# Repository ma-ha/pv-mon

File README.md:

# Monitor Photovoltaic (PV) System with LiFePO4 Batteries

Measure:
1. LiFePo4 cell and block voltage
2. Current and voltage from solar panel strings
3. 230 V output current 
4. 230 V fallback current

Send data via WiFi to local "IoT Server" and make data accessible in InfluxDB.

_STATUS: WIP, partially tested_

LiFePO4 (aka LFP) batteries are known as safe and the voltages may not be dangerous for humans.

**BUT ... WARNING: LFP batteries contain a lot of Energy! Shorts can cause enormous sparks, melt metal and cause fire.**

Check your circuits twice for shorts (soldering problems)! 
Be careful touching the circuit with metal tools (e.g. multimeter tips).
Put the circuit in a safe enclosure!

# Sensor Device

The device measures up to 16 voltages and sends them to the IoT Server. 

Hardware is cheap and simple, based on:
- an ESP8266 "D1 Mini" controller with WIFI
- a CD74HC4067 as 16 channel (or 74HC4051 as 8 channel) multiplexer board
- Pololu D36V6F3 Step-Down Voltage Regulator for 3.3 V supply

The sensor is designed to connect via a "8s JST XH " y-splitter cable between the
battery and the BMS. 
Alternatively connect Pin1 to "minus", Pin2 to the plus of 1st cell, Pin3 to the plus of 2nd cell and so on.

## Sensor Firmware

To upload the [firmware](sensor16ADC/bat-mon-firmware/bat-mon-firmware.ino) 
to the "D1 Mini" via the Arduino IDE, you must 
add `http://arduino.esp8266.com/stable/package_esp8266com_index.json` as 
"Additiona Boards Manager URLs" in the "File" > "Settings" menu. 
Then install the newest version in "Tools" > "Board" > "Board Manager" the "esp8266".
For me the "NodeMCU v0.9" board works fine.

Then just 
- connect the D1 Mini via USB 
- double click the [bat-mon-firmware.ino](sensor16ADC/bat-mon-firmware/bat-mon-firmware.ino) 
  to oben it in the Arduino IDE and 
- click the "Upload" button to compile the code and program the module

The sensor will read out the voltages once per minute and send them to the "IoT API Server".

WARNING: If you use the Arduino IDE for NodeMCU, you will overwrite the LUA SDK. 
If you want back the Lua SDK, use the “flasher” to re-install the firmware. 
You can download the flasher from their Github page https://github.com/nodemcu/nodemcu-flasher.

# Server Set Up

The "server" (a PC is ok) need to run an "[IoT API Server](iot-api-server/app.js)", 
where the sensors post readings data and an InfluxDB to store and analyze the data.

To make things as easy, I recommend to run the server and the DB as Docker containers.

## InfluxDB

The Influx DB stores the sensor data as timelines. 
You can query data and show data as graphs on dashboards using your browser.

Prepare a folders for DB, e.g. 

    mkdir ~/influxdb2
    cd ~/influxdb2
    mkdir db
    mkdir config
    export DB_DIR=$PWD

Start InfluxDB docker server:

    docker run -p 8086:8086 -d --restart=always --name influxdb \
      -v $DB_DIR/db:/var/lib/influxdb2 \
      -v $DB_DIR/config:/etc/influxdb2 \
      -e DOCKER_INFLUXDB_INIT_USERNAME=mysuerpadmin \
      -e DOCKER_INFLUXDB_INIT_PASSWORD=mysuerpadminpassord \
      -e DOCKER_INFLUXDB_INIT_ORG=my-org \
      -e DOCKER_INFLUXDB_INIT_BUCKET=pv \
      influxdb:2.1-alpine

Open http://localhost:8086 in your browser and finalize the set up.

Finally create or copy an API token for the API server, via "Data" manu and "API Tokens" tab.

## IoT API Server 

The "[API Server](iot-api-server/app.js)" is a tiny JS app and listens on 8899.

Devices can post JSON data to the endpoint 
`http:/server-ip:8899/<bucket>/<data-type>?key=<api-key>`

JSON data is e.g.:

    { src: 'Bat1_7', fld: 'U', val: 0.06 }

## Start on Console

Put the InfluxDB API key into the two YAML files in the `iot-api-server/config/` dir.

If you modify the `API_KEY`, don't forget to chage that also in the `bat-mon-firmware.ino`.

To start the server on the console for testing, execute:

    cd iot-api-server
    npm install
    export NODE_ENV=DEV
    node app.js

To send some test data execute: `mocha test/testPostApiSvr.js`

## Run as Docker Server

Build and install the IoT API Server:

    cd iot-api-server
    docker build -t mh/iot-api-server . 
    docker rm iot-api-server
    docker run -d -e NODE_ENV=MAIN --link influxdb:influxdb  -p 8899:8899  --name iot-api-server  mh/iot-api-server

To send some test data execute (require `npm install -g mocha` once): 

    export NODE_ENV=DEV
    mocha test/testPostApiSvr.js

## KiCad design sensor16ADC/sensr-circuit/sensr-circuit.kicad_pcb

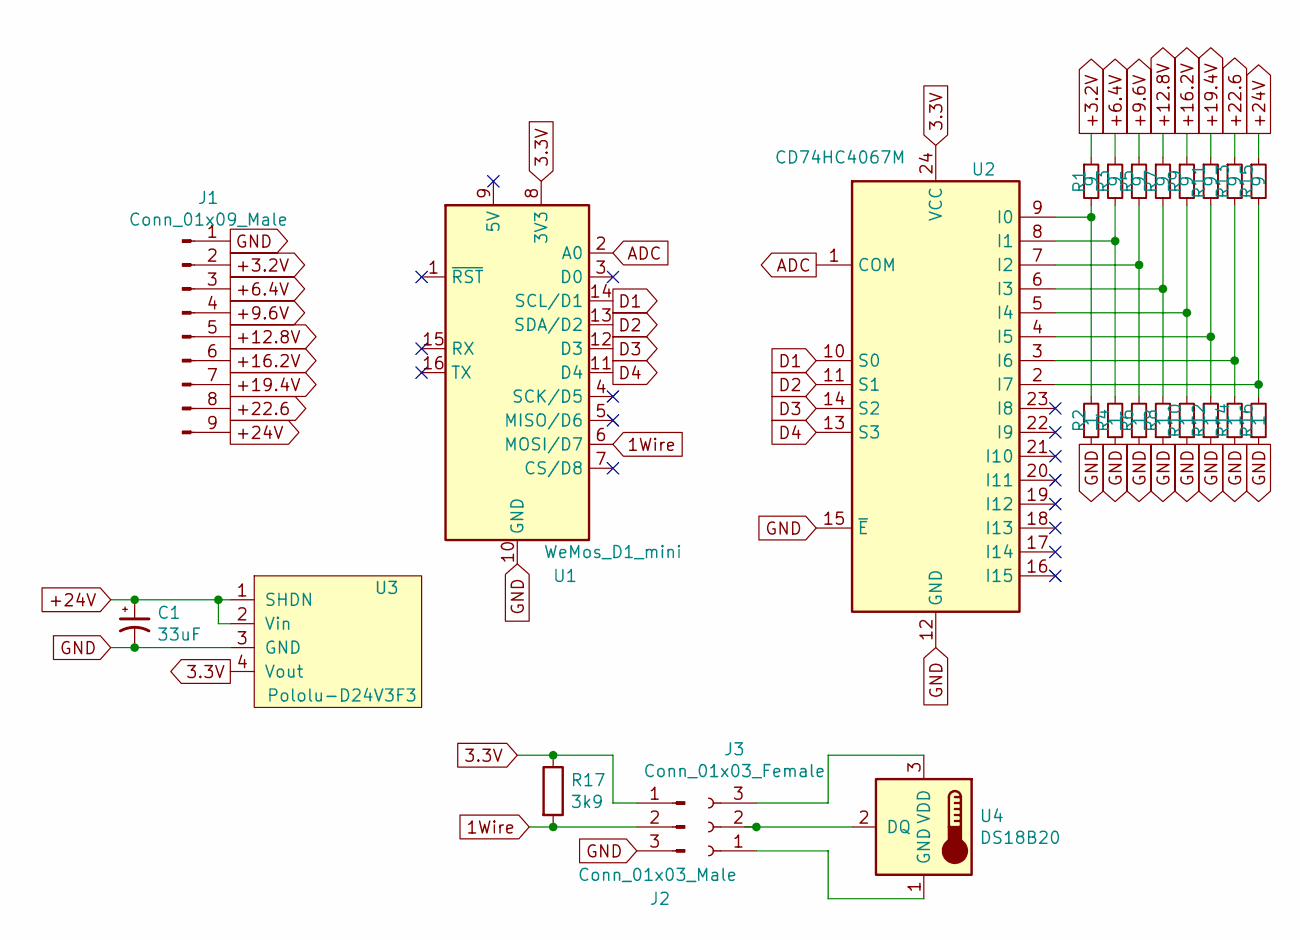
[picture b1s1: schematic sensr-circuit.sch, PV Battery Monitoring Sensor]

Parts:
C1: 33uF; CP_Radial_D5.0mm_P2.50mm
J1: Conn_01x09_Male; PinHeader_1x09_P2.54mm_Vertical
J2: Conn_01x03_Male; JST_EH_B3B-EH-A_1x03_P2.50mm_Vertical
J3: Conn_01x03_Female
R1, R3, R5, R7, R9, R11, R13, R15: 9; R_Axial_DIN0204_L3.6mm_D1.6mm_P7.62mm_Horizontal
R2, R4, R6, R8, R10, R12, R14, R16: 1; R_Axial_DIN0204_L3.6mm_D1.6mm_P7.62mm_Horizontal
R17: 3k9; R_Axial_DIN0309_L9.0mm_D3.2mm_P2.54mm_Vertical
U1: WeMos_D1_mini; WEMOS_D1_mini_light
U2: CD74HC4067M; 74HC4067DB
U3: Pololu-D24V3F3
U4: DS18B20

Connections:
1Wire: J2.2, R17.2, U1.6 (MOSI/D7)
3.3V: J2.1, R17.1, U1.8 (3V3), U2.24 (VCC), U3.4 (Vout)
+3.2V: J1.2, R1.1
+6.4V: J1.3, R3.1
+9.6V: J1.4, R5.1
+12.8V: J1.5, R7.1
+16.2V: J1.6, R9.1
+19.4V: J1.7, R11.1
+22.6: J1.8, R13.1
+24V: C1.1, J1.9, R15.1, U3.1 (SHDN), U3.2 (Vin)
ADC: U1.2 (A0), U2.1 (COM)
D1: U1.14 (SCL/D1), U2.10 (S0)
D2: U1.13 (SDA/D2), U2.11 (S1)
D3: U1.12 (D3), U2.14 (S2)
D4: U1.11 (D4), U2.13 (S3)
GND: C1.2, J1.1, J2.3, R2.1, R4.1, R6.1, R8.1, R10.1, R12.1, R14.1, R16.1, U1.10 (GND), U2.12 (GND), U2.15 (~E), U3.3 (GND)
unnamed: J3.1, U4.1 (GND)
unnamed: J3.2, U4.2 (DQ)
unnamed: J3.3, U4.3 (VDD)
unnamed: R1.2, R2.2, U2.9 (I0)
unnamed: R3.2, R4.2, U2.8 (I1)
unnamed: R5.2, R6.2, U2.7 (I2)
unnamed: R7.2, R8.2, U2.6 (I3)
unnamed: R9.2, R10.2, U2.5 (I4)
unnamed: R11.2, R12.2, U2.4 (I5)
unnamed: R13.2, R14.2, U2.3 (I6)
unnamed: R15.2, R16.2, U2.2 (I7)

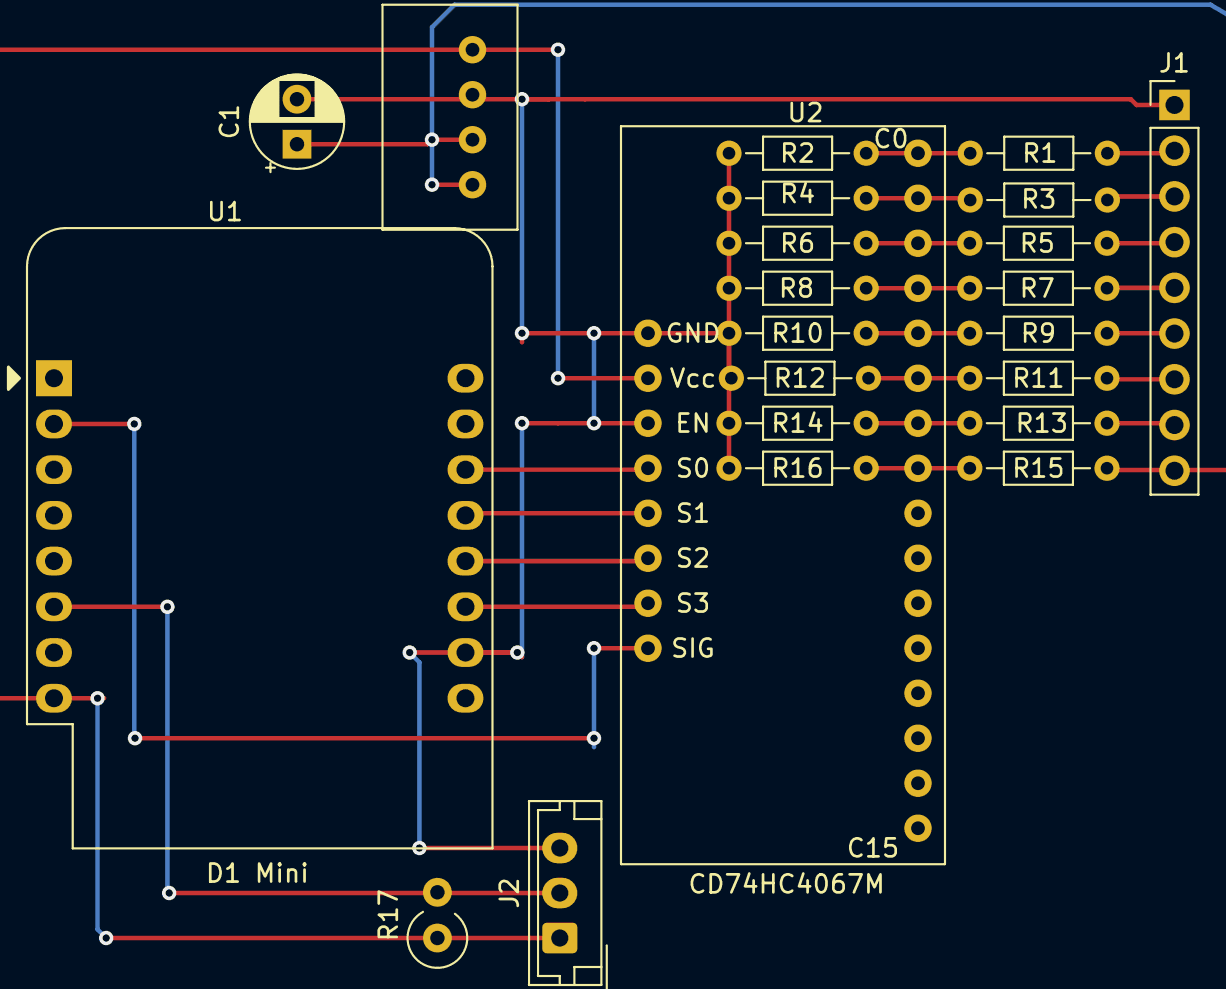
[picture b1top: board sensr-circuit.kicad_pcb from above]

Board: 2 copper layers, 23 parts (0 on the bottom side), 24 nets.

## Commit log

2022-03-20 publish 1st working version
2022-03-20 lazout for prototype board
2022-03-20 improve docu
2022-03-20 improved docu
2022-03-20 bat-mon-firmware:0.2.0 send total voltage
2022-03-22 circuit with 24V to 3.3V regulator
2022-03-25 circuit fix
2022-03-25 use Pololu D36V6F3 now
2022-03-26 bat-mon 0.3.0 fixes
2022-03-27 docu improved
2022-03-27 fix link
2022-03-27 fixe for docker
2022-04-02 bat-mon-fw:0.4.0 send battery charge percent
2022-04-04 bat-mon-firmware:0.5.0 Temperature sensor DS18B20
